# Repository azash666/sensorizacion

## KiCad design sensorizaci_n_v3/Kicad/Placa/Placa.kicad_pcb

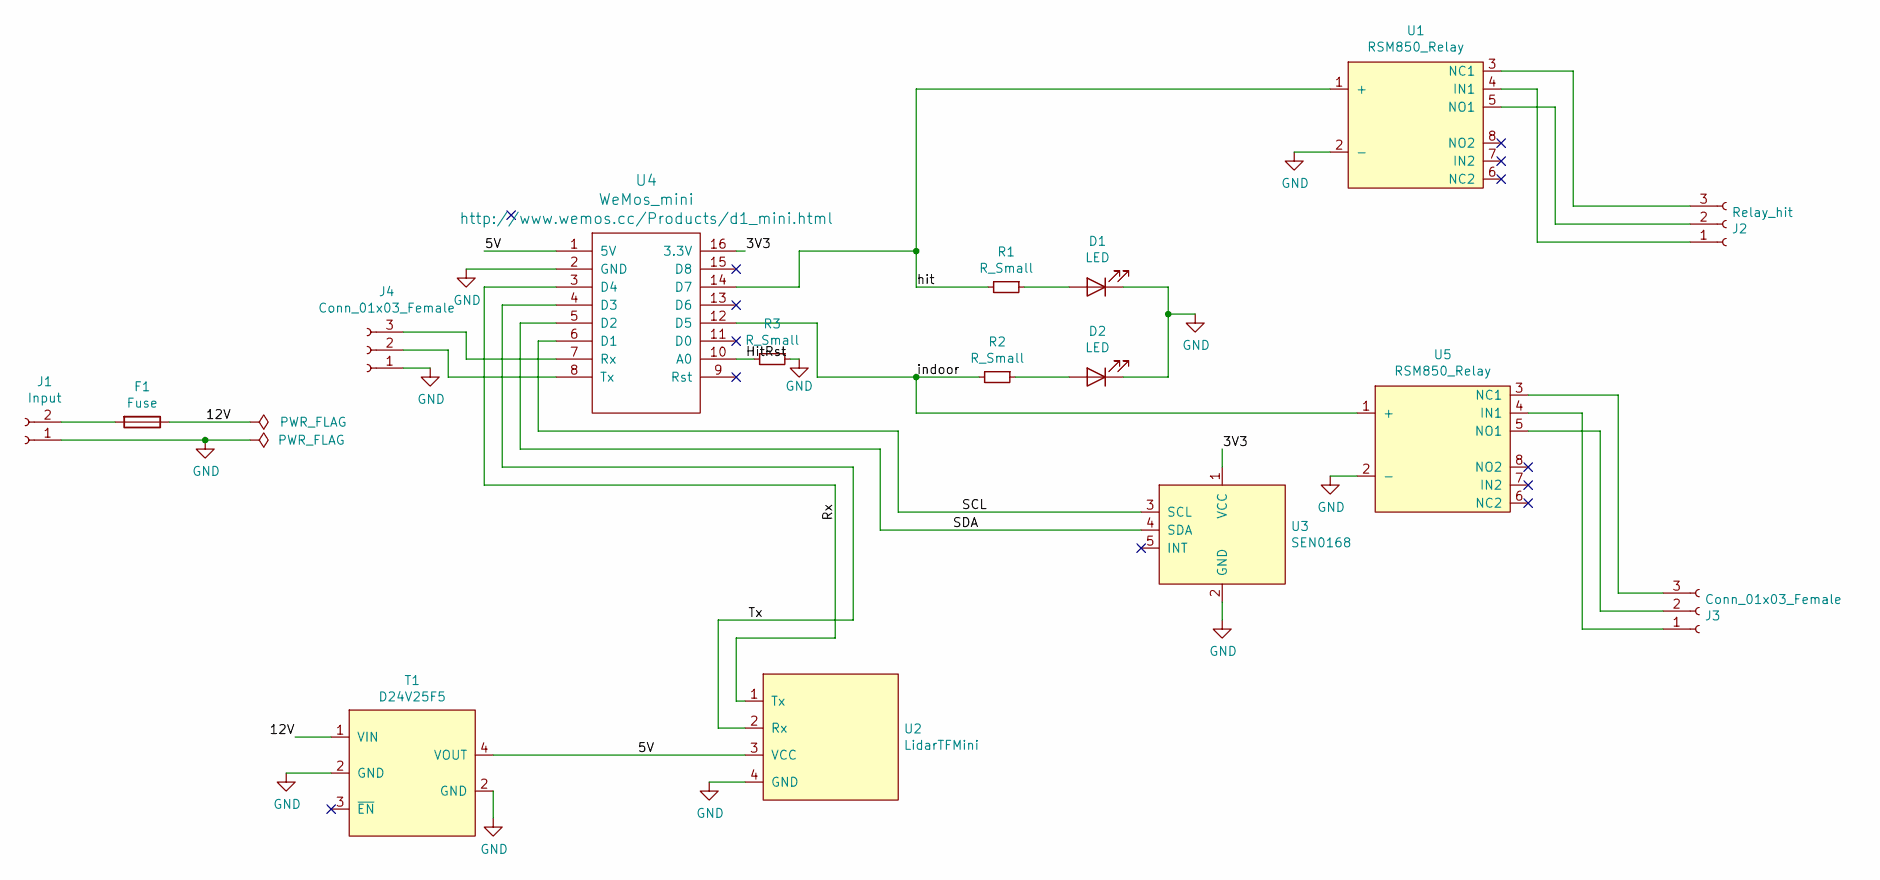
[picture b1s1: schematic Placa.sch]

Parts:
D1, D2: LED; LED_D1.8mm_W3.3mm_H2.4mm
F1: Fuse; Fuseholder_Blade_ATO_Littelfuse_Pudenz_2_Pin
J1: Input; PinHeader_1x02_P2.54mm_Vertical
J2: Relay_hit; PinHeader_1x03_P2.54mm_Vertical
J3, J4: Conn_01x03_Female; PinHeader_1x03_P2.54mm_Vertical
R1, R2, R3: R_Small; R_Axial_DIN0204_L3.6mm_D1.6mm_P5.08mm_Horizontal
T1: D24V25F5; Transformer_Pololu_D24V25Fx
U1, U5: RSM850_Relay
U2: LidarTFMini; PinHeader_1x04_P2.54mm_Vertical
U3: SEN0168
U4: WeMos_mini; wemos-d1-mini-with-pin-header-and-connector

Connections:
/3V3: U3.1 (VCC), U4.16 (3.3V)
/5V: T1.4 (VOUT), U2.3 (VCC), U4.1 (5V)
/12V: F1.1, T1.1 (VIN)
/HitRst: R3.2, U4.10 (A0)
/Rx: U2.1 (Tx), U4.3 (D4)
/SCL: U3.3 (SCL), U4.6 (D1)
/SDA: U3.4 (SDA), U4.5 (D2)
/Tx: U2.2 (Rx), U4.4 (D3)
/hit: R1.2, U1.1 (+), U4.14 (D7)
/indoor: R2.2, U4.12 (D5), U5.1 (+)
GND: D1.1 (K), D2.1 (K), J1.1, J4.1, R3.1, T1.2 (GND), U1.2 (-), U2.4 (GND), U3.2 (GND), U4.2 (GND), U5.2 (-)
unnamed: D1.2 (A), R1.1
unnamed: D2.2 (A), R2.1
unnamed: F1.2, J1.2
unnamed: J2.1, U1.4 (IN1)
unnamed: J2.2, U1.5 (NO1)
unnamed: J2.3, U1.3 (NC1)
unnamed: J3.1, U5.4 (IN1)
unnamed: J3.2, U5.5 (NO1)
unnamed: J3.3, U5.3 (NC1)
unnamed: J4.2, U4.8 (Tx)
unnamed: J4.3, U4.7 (Rx)

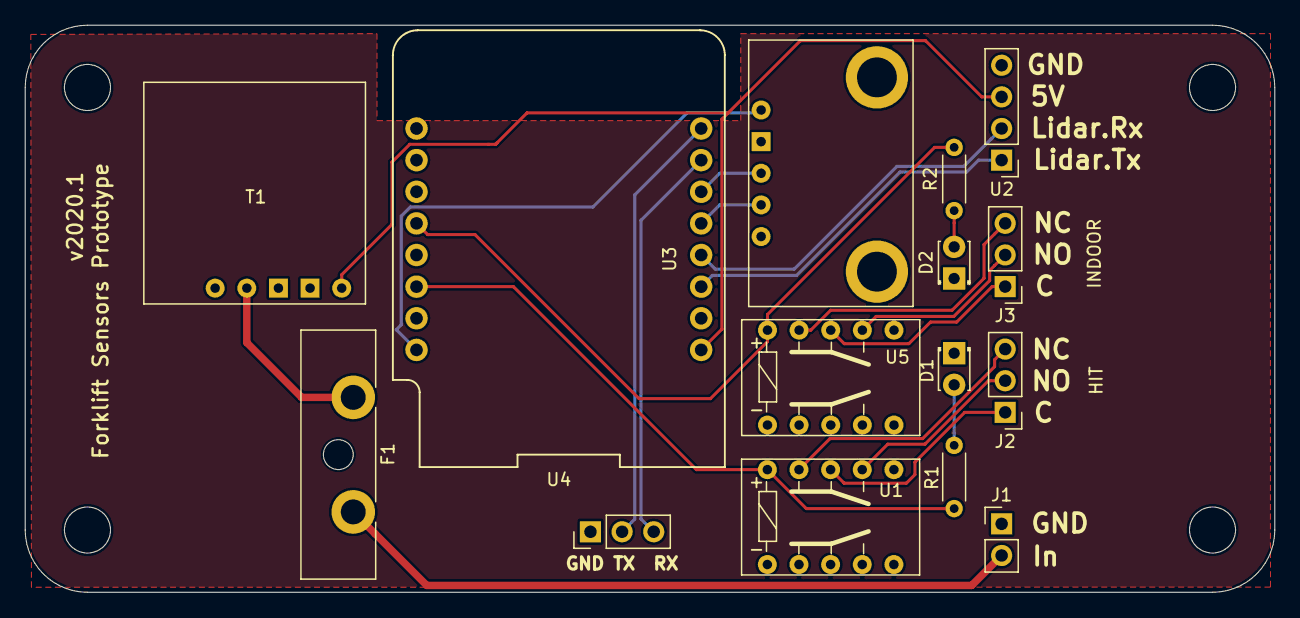
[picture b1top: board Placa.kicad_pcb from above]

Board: 2 copper layers, 100.3 x 45.5 mm, 15 parts (0 on the bottom side), 21 nets.
